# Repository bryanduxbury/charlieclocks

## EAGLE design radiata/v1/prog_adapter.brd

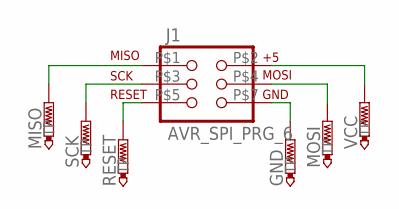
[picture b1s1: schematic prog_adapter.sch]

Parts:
GND: PTR1PAD1-17; P1-17
J1: AVR_SPI_PRG_6; 2X3_ICSP_SMD
MISO: PTR1PAD1-17; P1-17
MOSI: PTR1PAD1-17; P1-17
RESET: PTR1PAD1-17; P1-17
SCK: PTR1PAD1-17; P1-17
VCC: PTR1PAD1-17; P1-17

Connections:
unnamed: J1.P$1 (1), MISO.TP
unnamed: J1.P$3 (3), SCK.TP
unnamed: J1.P$5 (5), RESET.TP
unnamed: J1.P$2 (2), VCC.TP
unnamed: J1.P$4 (4), MOSI.TP
unnamed: GND.TP, J1.P$7 (6)

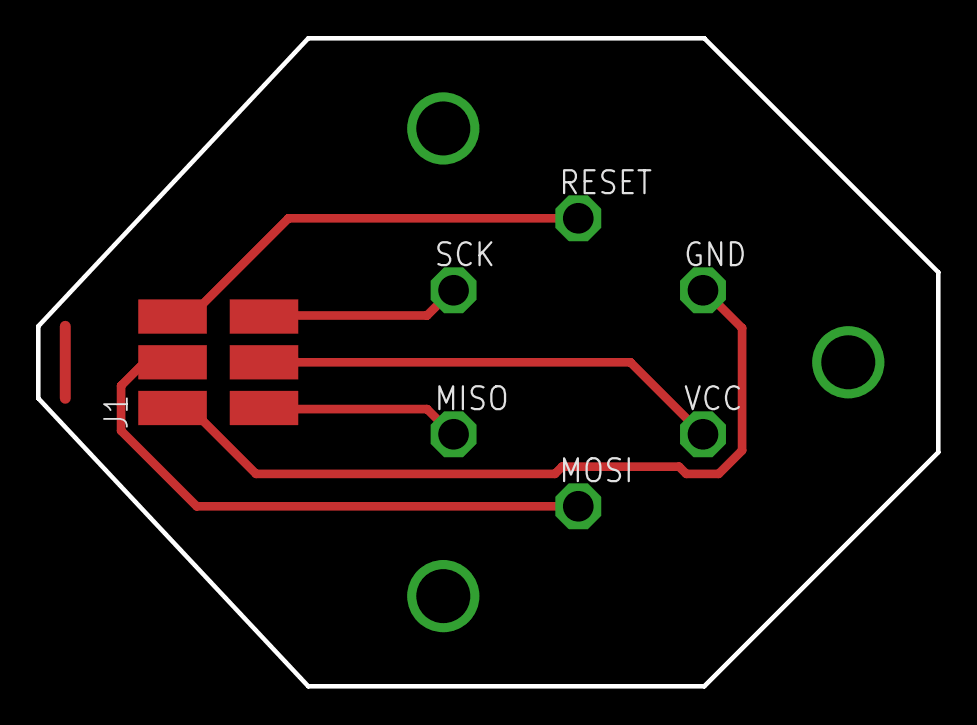
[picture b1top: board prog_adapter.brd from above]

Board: 2 copper layers, 50.0 x 36.0 mm, 7 parts (0 on the bottom side), 6 nets.

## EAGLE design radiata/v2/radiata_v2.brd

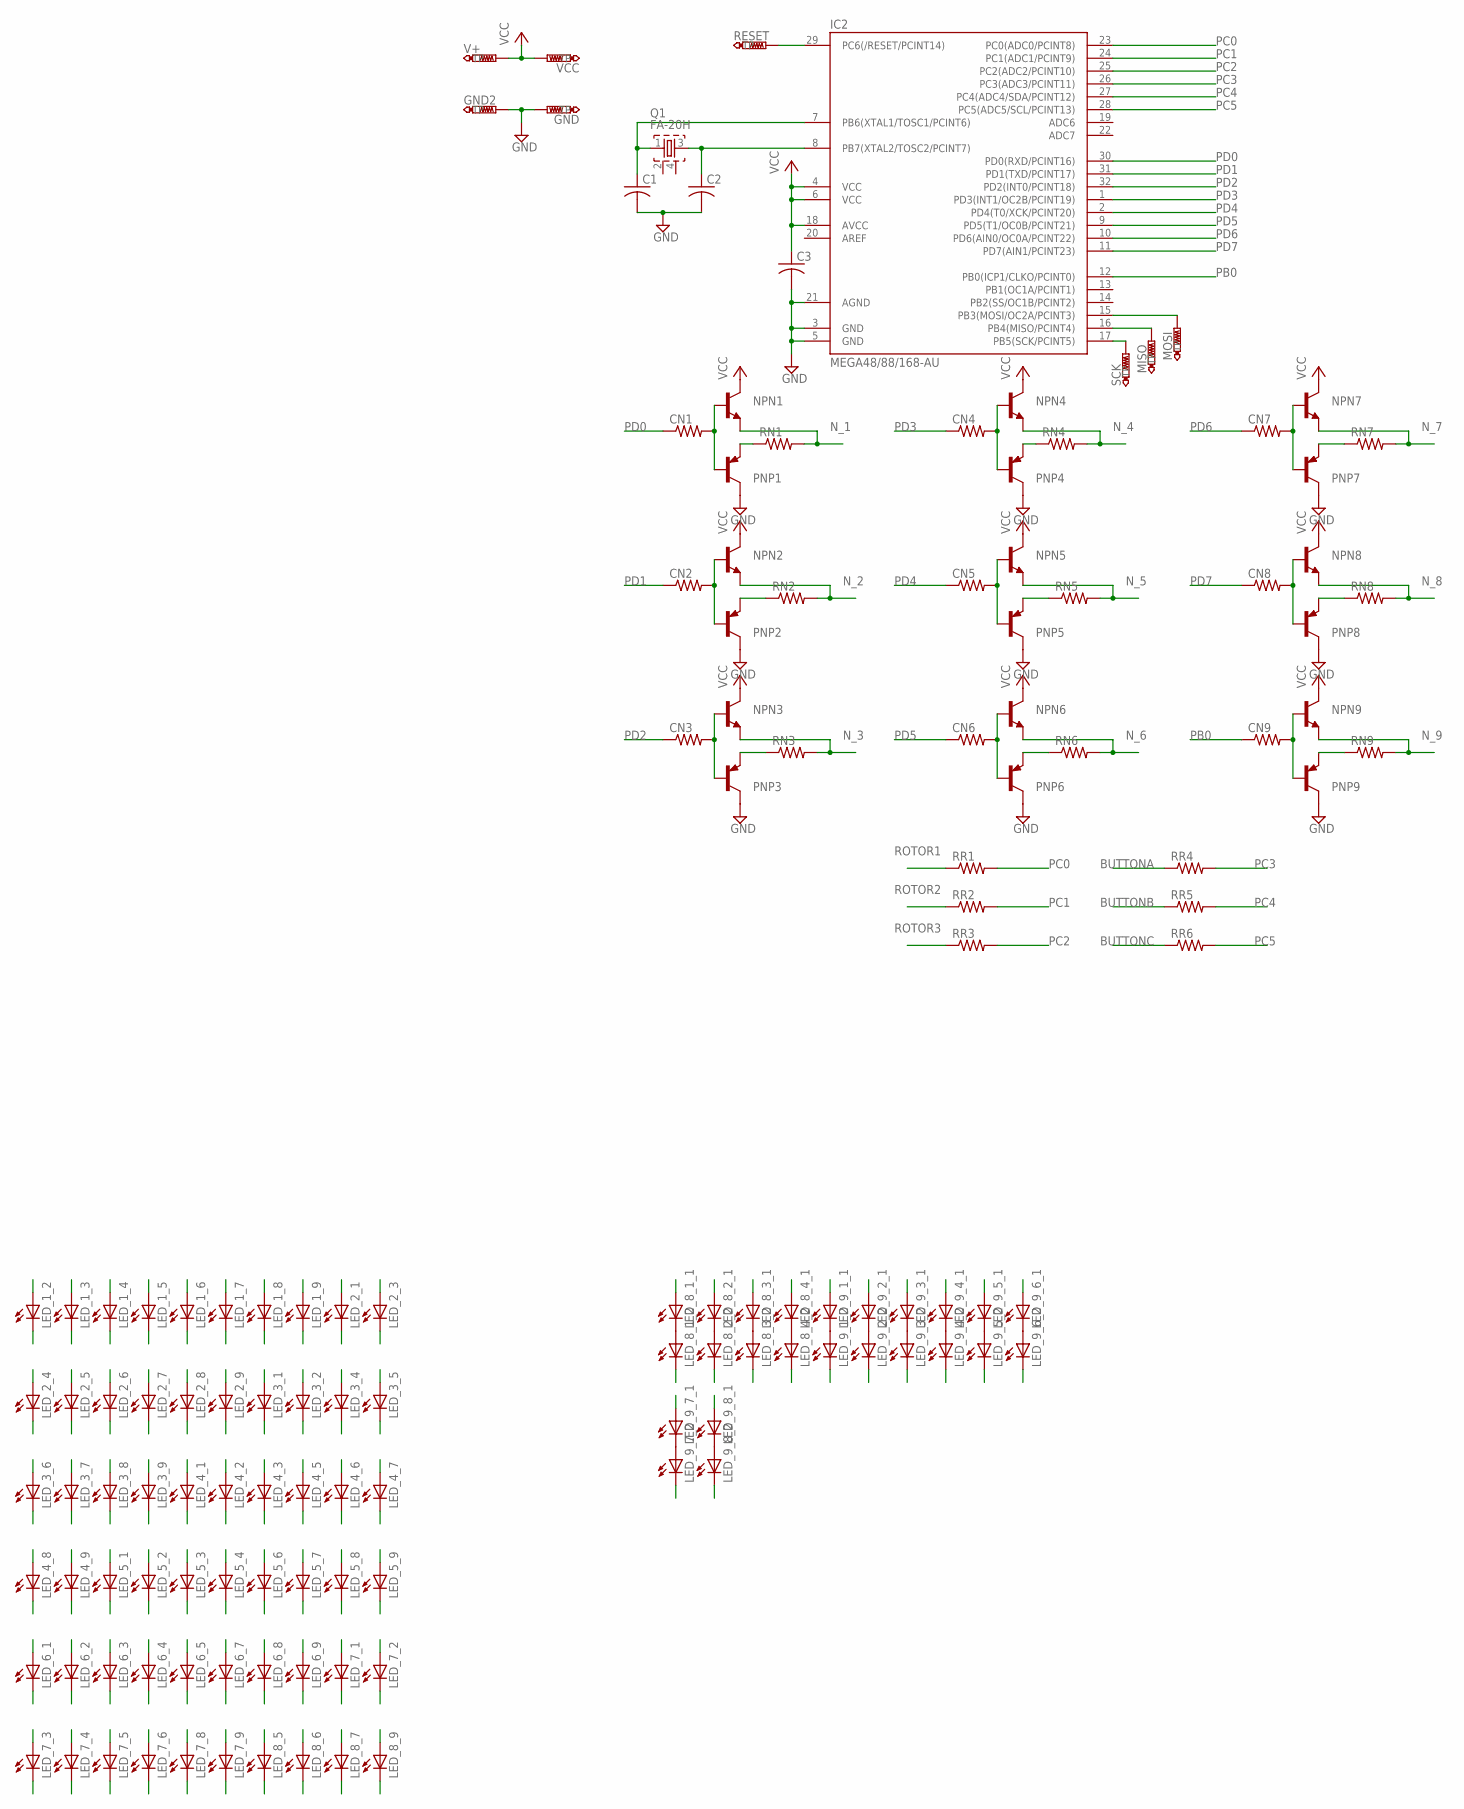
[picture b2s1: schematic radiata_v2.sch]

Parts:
C1, C2, C3: C-USC0603; C0603
CN1, CN2, CN3, CN4, CN5, CN6, CN7, CN8, CN9: R-US_M0805; M0805
GND: PTR1TP19R; TP19R
GND2: PTR1TP20SQ; TP20SQ
IC2: MEGA48/88/168-AU; TQFP32-08
LED_1_2, LED_1_3, LED_1_4, LED_1_5, LED_1_6, LED_1_7, LED_1_8, LED_1_9, LED_2_1, LED_2_3, LED_2_4, LED_2_5, LED_2_6, LED_2_7, LED_2_8, LED_2_9, LED_3_1, LED_3_2, LED_3_4, LED_3_5, LED_3_6, LED_3_7, LED_3_8, LED_3_9, LED_4_1, LED_4_2, LED_4_3, LED_4_5, LED_4_6, LED_4_7, LED_4_8, LED_4_9, LED_5_1, LED_5_2, LED_5_3, LED_5_4, LED_5_6, LED_5_7, LED_5_8, LED_5_9, LED_6_1, LED_6_2, LED_6_3, LED_6_4, LED_6_5, LED_6_7, LED_6_8, LED_6_9, LED_7_1, LED_7_2, LED_7_3, LED_7_4, LED_7_5, LED_7_6, LED_7_8, LED_7_9, LED_8_1_1, LED_8_1_2, LED_8_2_1, LED_8_2_2, LED_8_3_1, LED_8_3_2, LED_8_4_1, LED_8_4_2, LED_8_5, LED_8_6, LED_8_7, LED_8_9, LED_9_1_1, LED_9_1_2, LED_9_2_1, LED_9_2_2, LED_9_3_1, LED_9_3_2, LED_9_4_1, LED_9_4_2, LED_9_5_1, LED_9_5_2, LED_9_6_1, LED_9_6_2, LED_9_7_1, LED_9_7_2, LED_9_8_1, LED_9_8_2: LED1206; LED-1206
MISO: PTR1TP19R; TP19R
MOSI: PTR1TP19R; TP19R
NPN1, NPN2, NPN3, NPN4, NPN5, NPN6, NPN7, NPN8, NPN9: MMBT2222ALT1-NPN-SOT23-BEC; SOT23-BEC
PNP1, PNP2, PNP3, PNP4, PNP5, PNP6, PNP7, PNP8, PNP9: MMBT2907ALT1-PNP-SOT23-BEC; SOT23-BEC
Q1: FA-20H
RESET: PTR1TP19R; TP19R
RN1, RN2, RN3, RN4, RN5, RN6, RN7, RN8, RN9: RESISTOR1206; 1206
RR1, RR2, RR3, RR4, RR5, RR6: RESISTOR1206; 1206
SCK: PTR1TP19R; TP19R
V+: PTR1TP20SQ; TP20SQ
VCC: PTR1TP19R; TP19R

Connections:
BUTTONA: RR4.1
BUTTONB: RR5.1
BUTTONC: RR6.1
GND: C1.2, C2.2, C3.2, GND.TP, GND2.TP, IC2.3 (GND), IC2.5 (GND), IC2.21 (AGND), PNP1.C, PNP2.C, PNP3.C, PNP4.C, PNP5.C, PNP6.C, PNP7.C, PNP8.C, PNP9.C
unnamed: IC2.29 (PC6(/RESET/PCINT14)), RESET.TP
unnamed: IC2.17 (PB5(SCK/PCINT5)), SCK.TP
unnamed: IC2.16 (PB4(MISO/PCINT4)), MISO.TP
unnamed: IC2.15 (PB3(MOSI/OC2A/PCINT3)), MOSI.TP
unnamed: PNP1.E, RN1.1
unnamed: CN1.2, NPN1.B, PNP1.B
unnamed: PNP2.E, RN2.1
unnamed: CN2.2, NPN2.B, PNP2.B
unnamed: PNP3.E, RN3.1
unnamed: CN3.2, NPN3.B, PNP3.B
unnamed: PNP4.E, RN4.1
unnamed: CN4.2, NPN4.B, PNP4.B
unnamed: PNP5.E, RN5.1
unnamed: CN5.2, NPN5.B, PNP5.B
unnamed: PNP6.E, RN6.1
unnamed: CN6.2, NPN6.B, PNP6.B
unnamed: C2.1, IC2.8 (PB7(XTAL2/TOSC2/PCINT7)), Q1.3
unnamed: LED_8_1_1.C, LED_8_1_2.A
unnamed: LED_8_2_1.C, LED_8_2_2.A
unnamed: PNP7.E, RN7.1
unnamed: CN7.2, NPN7.B, PNP7.B
unnamed: PNP8.E, RN8.1
unnamed: CN8.2, NPN8.B, PNP8.B
unnamed: PNP9.E, RN9.1
unnamed: CN9.2, NPN9.B, PNP9.B
unnamed: LED_8_3_1.C, LED_8_3_2.A
unnamed: LED_8_4_1.C, LED_8_4_2.A
unnamed: LED_9_1_1.C, LED_9_1_2.A
unnamed: LED_9_2_1.C, LED_9_2_2.A
unnamed: LED_9_3_1.C, LED_9_3_2.A
unnamed: LED_9_4_1.C, LED_9_4_2.A
unnamed: LED_9_5_1.C, LED_9_5_2.A
unnamed: LED_9_6_1.C, LED_9_6_2.A
unnamed: LED_9_7_1.C, LED_9_7_2.A
unnamed: LED_9_8_1.C, LED_9_8_2.A
N_1: LED_1_2.A, LED_1_3.A, LED_1_4.A, LED_1_5.A, LED_1_6.A, LED_1_7.A, LED_1_8.A, LED_1_9.A, LED_2_1.C, LED_3_1.C, LED_4_1.C, LED_5_1.C, LED_6_1.C, LED_7_1.C, LED_8_1_2.C, LED_9_1_2.C, NPN1.E, RN1.2
N_2: LED_1_2.C, LED_2_1.A, LED_2_3.A, LED_2_4.A, LED_2_5.A, LED_2_6.A, LED_2_7.A, LED_2_8.A, LED_2_9.A, LED_3_2.C, LED_4_2.C, LED_5_2.C, LED_6_2.C, LED_7_2.C, LED_8_2_2.C, LED_9_2_2.C, NPN2.E, RN2.2
N_3: LED_1_3.C, LED_2_3.C, LED_3_1.A, LED_3_2.A, LED_3_4.A, LED_3_5.A, LED_3_6.A, LED_3_7.A, LED_3_8.A, LED_3_9.A, LED_4_3.C, LED_5_3.C, LED_6_3.C, LED_7_3.C, LED_8_3_2.C, LED_9_3_2.C, NPN3.E, RN3.2
N_4: LED_1_4.C, LED_2_4.C, LED_3_4.C, LED_4_1.A, LED_4_2.A, LED_4_3.A, LED_4_5.A, LED_4_6.A, LED_4_7.A, LED_4_8.A, LED_4_9.A, LED_5_4.C, LED_6_4.C, LED_7_4.C, LED_8_4_2.C, LED_9_4_2.C, NPN4.E, RN4.2
N_5: LED_1_5.C, LED_2_5.C, LED_3_5.C, LED_4_5.C, LED_5_1.A, LED_5_2.A, LED_5_3.A, LED_5_4.A, LED_5_6.A, LED_5_7.A, LED_5_8.A, LED_5_9.A, LED_6_5.C, LED_7_5.C, LED_8_5.C, LED_9_5_2.C, NPN5.E, RN5.2
N_6: LED_1_6.C, LED_2_6.C, LED_3_6.C, LED_4_6.C, LED_5_6.C, LED_6_1.A, LED_6_2.A, LED_6_3.A, LED_6_4.A, LED_6_5.A, LED_6_7.A, LED_6_8.A, LED_6_9.A, LED_7_6.C, LED_8_6.C, LED_9_6_2.C, NPN6.E, RN6.2
N_7: LED_1_7.C, LED_2_7.C, LED_3_7.C, LED_4_7.C, LED_5_7.C, LED_6_7.C, LED_7_1.A, LED_7_2.A, LED_7_3.A, LED_7_4.A, LED_7_5.A, LED_7_6.A, LED_7_8.A, LED_7_9.A, LED_8_7.C, LED_9_7_2.C, NPN7.E, RN7.2
N_8: LED_1_8.C, LED_2_8.C, LED_3_8.C, LED_4_8.C, LED_5_8.C, LED_6_8.C, LED_7_8.C, LED_8_1_1.A, LED_8_2_1.A, LED_8_3_1.A, LED_8_4_1.A, LED_8_5.A, LED_8_6.A, LED_8_7.A, LED_8_9.A, LED_9_8_2.C, NPN8.E, RN8.2
N_9: LED_1_9.C, LED_2_9.C, LED_3_9.C, LED_4_9.C, LED_5_9.C, LED_6_9.C, LED_7_9.C, LED_8_9.C, LED_9_1_1.A, LED_9_2_1.A, LED_9_3_1.A, LED_9_4_1.A, LED_9_5_1.A, LED_9_6_1.A, LED_9_7_1.A, LED_9_8_1.A, NPN9.E, RN9.2
PB0: CN9.1, IC2.12 (PB0(ICP1/CLKO/PCINT0))
PB1: C1.1, IC2.7 (PB6(XTAL1/TOSC1/PCINT6)), Q1.1
PC0: IC2.23 (PC0(ADC0/PCINT8)), RR1.2
PC1: IC2.24 (PC1(ADC1/PCINT9)), RR2.2
PC2: IC2.25 (PC2(ADC2/PCINT10)), RR3.2
PC3: IC2.26 (PC3(ADC3/PCINT11)), RR4.2
PC4: IC2.27 (PC4(ADC4/SDA/PCINT12)), RR5.2
PC5: IC2.28 (PC5(ADC5/SCL/PCINT13)), RR6.2
PD0: CN1.1, IC2.30 (PD0(RXD/PCINT16))
PD1: CN2.1, IC2.31 (PD1(TXD/PCINT17))
PD2: CN3.1, IC2.32 (PD2(INT0/PCINT18))
PD3: CN4.1, IC2.1 (PD3(INT1/OC2B/PCINT19))
PD4: CN5.1, IC2.2 (PD4(T0/XCK/PCINT20))
PD5: CN6.1, IC2.9 (PD5(T1/OC0B/PCINT21))
PD6: CN7.1, IC2.10 (PD6(AIN0/OC0A/PCINT22))
PD7: CN8.1, IC2.11 (PD7(AIN1/PCINT23))
ROTOR1: RR1.1
ROTOR2: RR2.1
ROTOR3: RR3.1
VCC: C3.1, IC2.4 (VCC), IC2.6 (VCC), IC2.18 (AVCC), NPN1.C, NPN2.C, NPN3.C, NPN4.C, NPN5.C, NPN6.C, NPN7.C, NPN8.C, NPN9.C, V+.TP, VCC.TP

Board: 2 copper layers, 139 parts (15 on the bottom side), 62 nets, no tracks yet.

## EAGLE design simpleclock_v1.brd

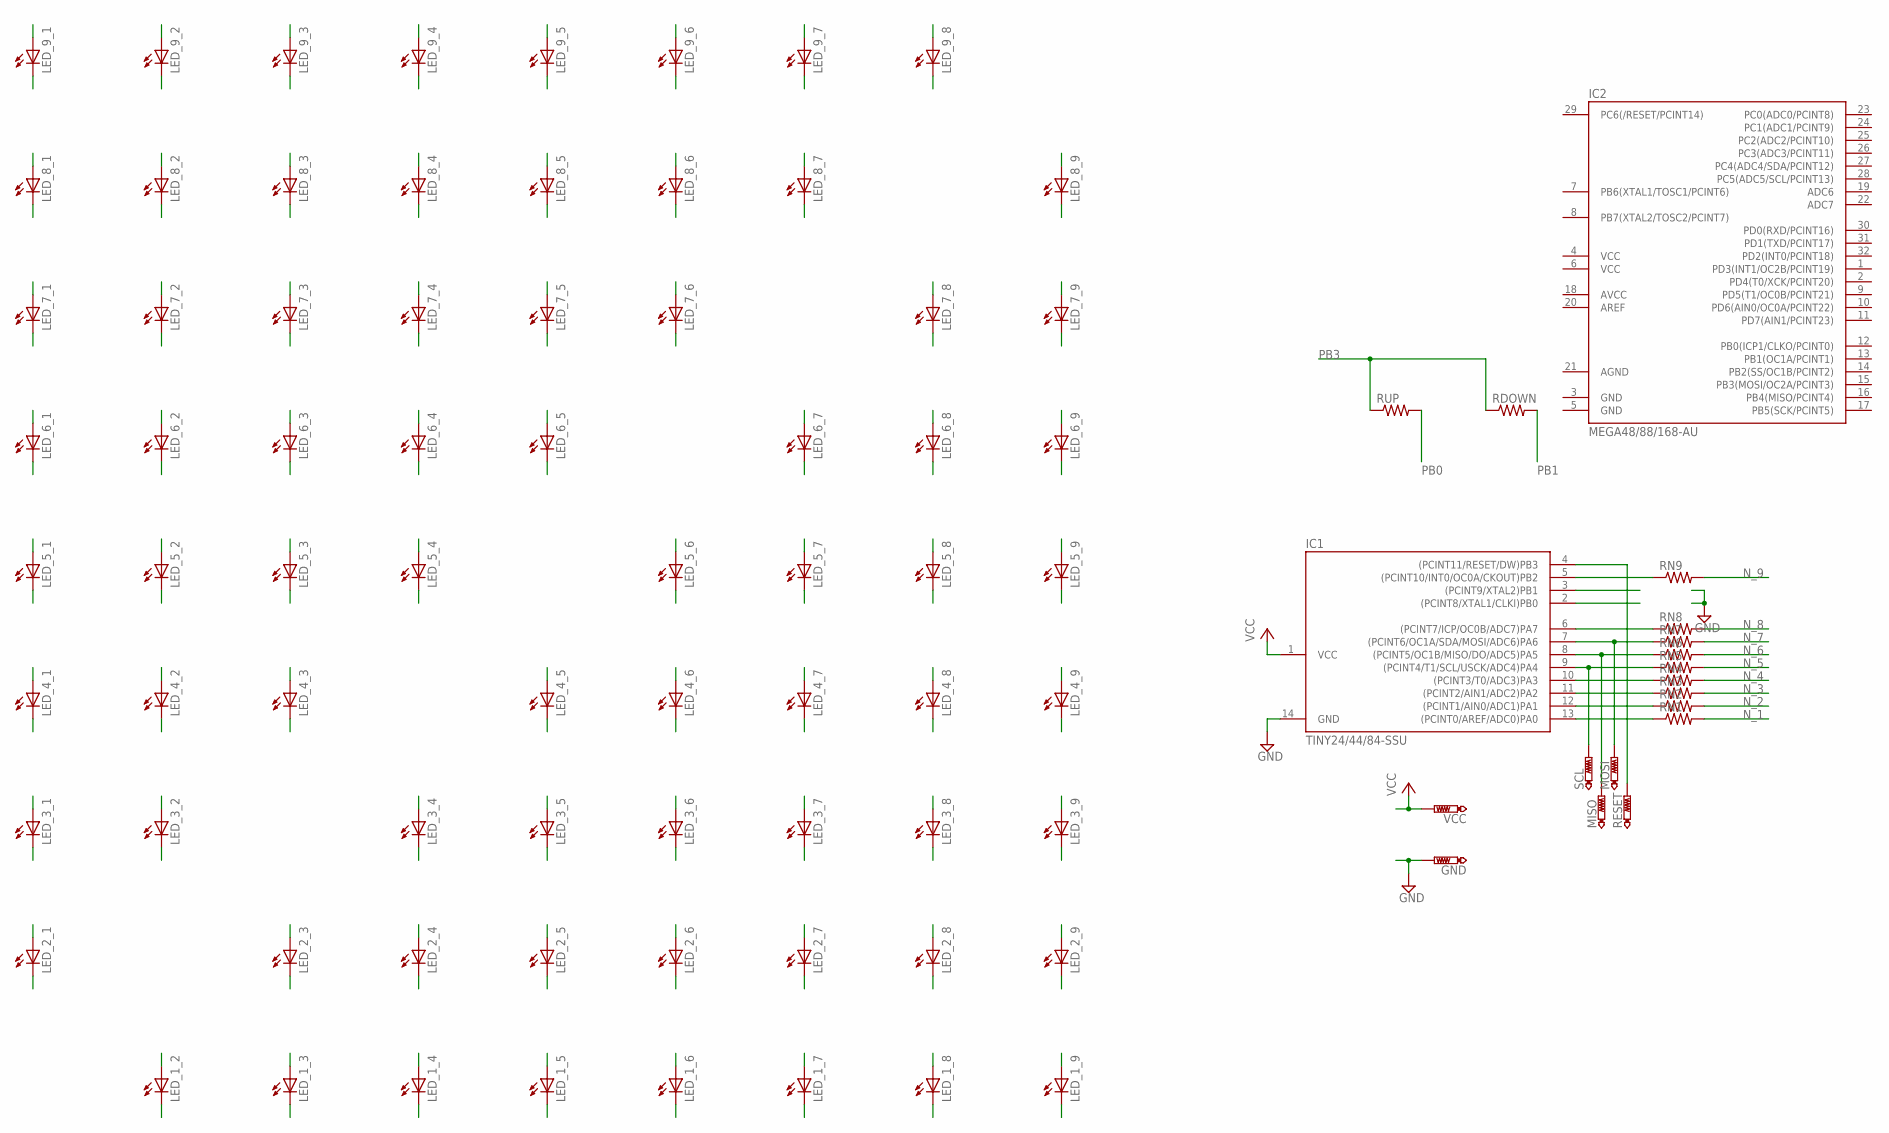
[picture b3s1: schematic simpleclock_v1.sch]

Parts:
GND: PTR1PAD1-13; P1-13
IC1: TINY24/44/84-SSU; SOIC14
IC2: MEGA48/88/168-AU; TQFP32-08
LED_1_2, LED_1_3, LED_1_4, LED_1_5, LED_1_6, LED_1_7, LED_1_8, LED_1_9, LED_2_1, LED_2_3, LED_2_4, LED_2_5, LED_2_6, LED_2_7, LED_2_8, LED_2_9, LED_3_1, LED_3_2, LED_3_4, LED_3_5, LED_3_6, LED_3_7, LED_3_8, LED_3_9, LED_4_1, LED_4_2, LED_4_3, LED_4_5, LED_4_6, LED_4_7, LED_4_8, LED_4_9, LED_5_1, LED_5_2, LED_5_3, LED_5_4, LED_5_6, LED_5_7, LED_5_8, LED_5_9, LED_6_1, LED_6_2, LED_6_3, LED_6_4, LED_6_5, LED_6_7, LED_6_8, LED_6_9, LED_7_1, LED_7_2, LED_7_3, LED_7_4, LED_7_5, LED_7_6, LED_7_8, LED_7_9, LED_8_1, LED_8_2, LED_8_3, LED_8_4, LED_8_5, LED_8_6, LED_8_7, LED_8_9, LED_9_1, LED_9_2, LED_9_3, LED_9_4, LED_9_5, LED_9_6, LED_9_7, LED_9_8: LEDCHIPLED_1206; CHIPLED_1206
MISO: PTR1PAD1-13; P1-13
MOSI: PTR1PAD1-13; P1-13
RDOWN: RESISTOR1206; 1206
RESET: PTR1PAD1-13; P1-13
RN1, RN2, RN3, RN4, RN5, RN6, RN7, RN8, RN9: RESISTOR1206; 1206
RUP: RESISTOR1206; 1206
SCL: PTR1PAD1-13; P1-13
VCC: PTR1PAD1-13; P1-13

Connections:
AGND: IC2.21 (AGND)
GND: GND.TP, IC1.14 (GND), IC2.3 (GND), IC2.5 (GND)
N_1: LED_1_2.A, LED_1_3.A, LED_1_4.A, LED_1_5.A, LED_1_6.A, LED_1_7.A, LED_1_8.A, LED_1_9.A, LED_2_1.C, LED_3_1.C, LED_4_1.C, LED_5_1.C, LED_6_1.C, LED_7_1.C, LED_8_1.C, LED_9_1.C, RN1.2
N_2: LED_1_2.C, LED_2_1.A, LED_2_3.A, LED_2_4.A, LED_2_5.A, LED_2_6.A, LED_2_7.A, LED_2_8.A, LED_2_9.A, LED_3_2.C, LED_4_2.C, LED_5_2.C, LED_6_2.C, LED_7_2.C, LED_8_2.C, LED_9_2.C, RN2.2
N_3: LED_1_3.C, LED_2_3.C, LED_3_1.A, LED_3_2.A, LED_3_4.A, LED_3_5.A, LED_3_6.A, LED_3_7.A, LED_3_8.A, LED_3_9.A, LED_4_3.C, LED_5_3.C, LED_6_3.C, LED_7_3.C, LED_8_3.C, LED_9_3.C, RN3.2
N_4: LED_1_4.C, LED_2_4.C, LED_3_4.C, LED_4_1.A, LED_4_2.A, LED_4_3.A, LED_4_5.A, LED_4_6.A, LED_4_7.A, LED_4_8.A, LED_4_9.A, LED_5_4.C, LED_6_4.C, LED_7_4.C, LED_8_4.C, LED_9_4.C, RN4.2
N_5: LED_1_5.C, LED_2_5.C, LED_3_5.C, LED_4_5.C, LED_5_1.A, LED_5_2.A, LED_5_3.A, LED_5_4.A, LED_5_6.A, LED_5_7.A, LED_5_8.A, LED_5_9.A, LED_6_5.C, LED_7_5.C, LED_8_5.C, LED_9_5.C, RN5.2
N_6: LED_1_6.C, LED_2_6.C, LED_3_6.C, LED_4_6.C, LED_5_6.C, LED_6_1.A, LED_6_2.A, LED_6_3.A, LED_6_4.A, LED_6_5.A, LED_6_7.A, LED_6_8.A, LED_6_9.A, LED_7_6.C, LED_8_6.C, LED_9_6.C, RN6.2
N_7: LED_1_7.C, LED_2_7.C, LED_3_7.C, LED_4_7.C, LED_5_7.C, LED_6_7.C, LED_7_1.A, LED_7_2.A, LED_7_3.A, LED_7_4.A, LED_7_5.A, LED_7_6.A, LED_7_8.A, LED_7_9.A, LED_8_7.C, LED_9_7.C, RN7.2
N_8: LED_1_8.C, LED_2_8.C, LED_3_8.C, LED_4_8.C, LED_5_8.C, LED_6_8.C, LED_7_8.C, LED_8_1.A, LED_8_2.A, LED_8_3.A, LED_8_4.A, LED_8_5.A, LED_8_6.A, LED_8_7.A, LED_8_9.A, LED_9_8.C, RN8.2
N_9: LED_1_9.C, LED_2_9.C, LED_3_9.C, LED_4_9.C, LED_5_9.C, LED_6_9.C, LED_7_9.C, LED_8_9.C, LED_9_1.A, LED_9_2.A, LED_9_3.A, LED_9_4.A, LED_9_5.A, LED_9_6.A, LED_9_7.A, LED_9_8.A, RN9.2
PA0: IC1.13 ((PCINT0/AREF/ADC0)PA0), RN1.1
PA1: IC1.12 ((PCINT1/AIN0/ADC1)PA1), RN2.1
PA2: IC1.11 ((PCINT2/AIN1/ADC2)PA2), RN3.1
PA3: IC1.10 ((PCINT3/T0/ADC3)PA3), RN4.1
PA4: IC1.9 ((PCINT4/T1/SCL/USCK/ADC4)PA4), RN5.1, SCL.TP
PA5: IC1.8 ((PCINT5/OC1B/MISO/DO/ADC5)PA5), MISO.TP, RN6.1
PA6: IC1.7 ((PCINT6/OC1A/SDA/MOSI/ADC6)PA6), MOSI.TP, RN7.1
PA7: IC1.6 ((PCINT7/ICP/OC0B/ADC7)PA7), RN8.1
PB0: IC1.2 ((PCINT8/XTAL1/CLKI)PB0), RUP.2
PB1: IC1.3 ((PCINT9/XTAL2)PB1), RDOWN.2
PB2: IC1.5 ((PCINT10/INT0/OC0A/CKOUT)PB2), RN9.1
PB3: IC1.4 ((PCINT11/RESET/DW)PB3), RDOWN.1, RESET.TP, RUP.1
VCC: IC1.1 (VCC), IC2.4 (VCC), IC2.6 (VCC), VCC.TP

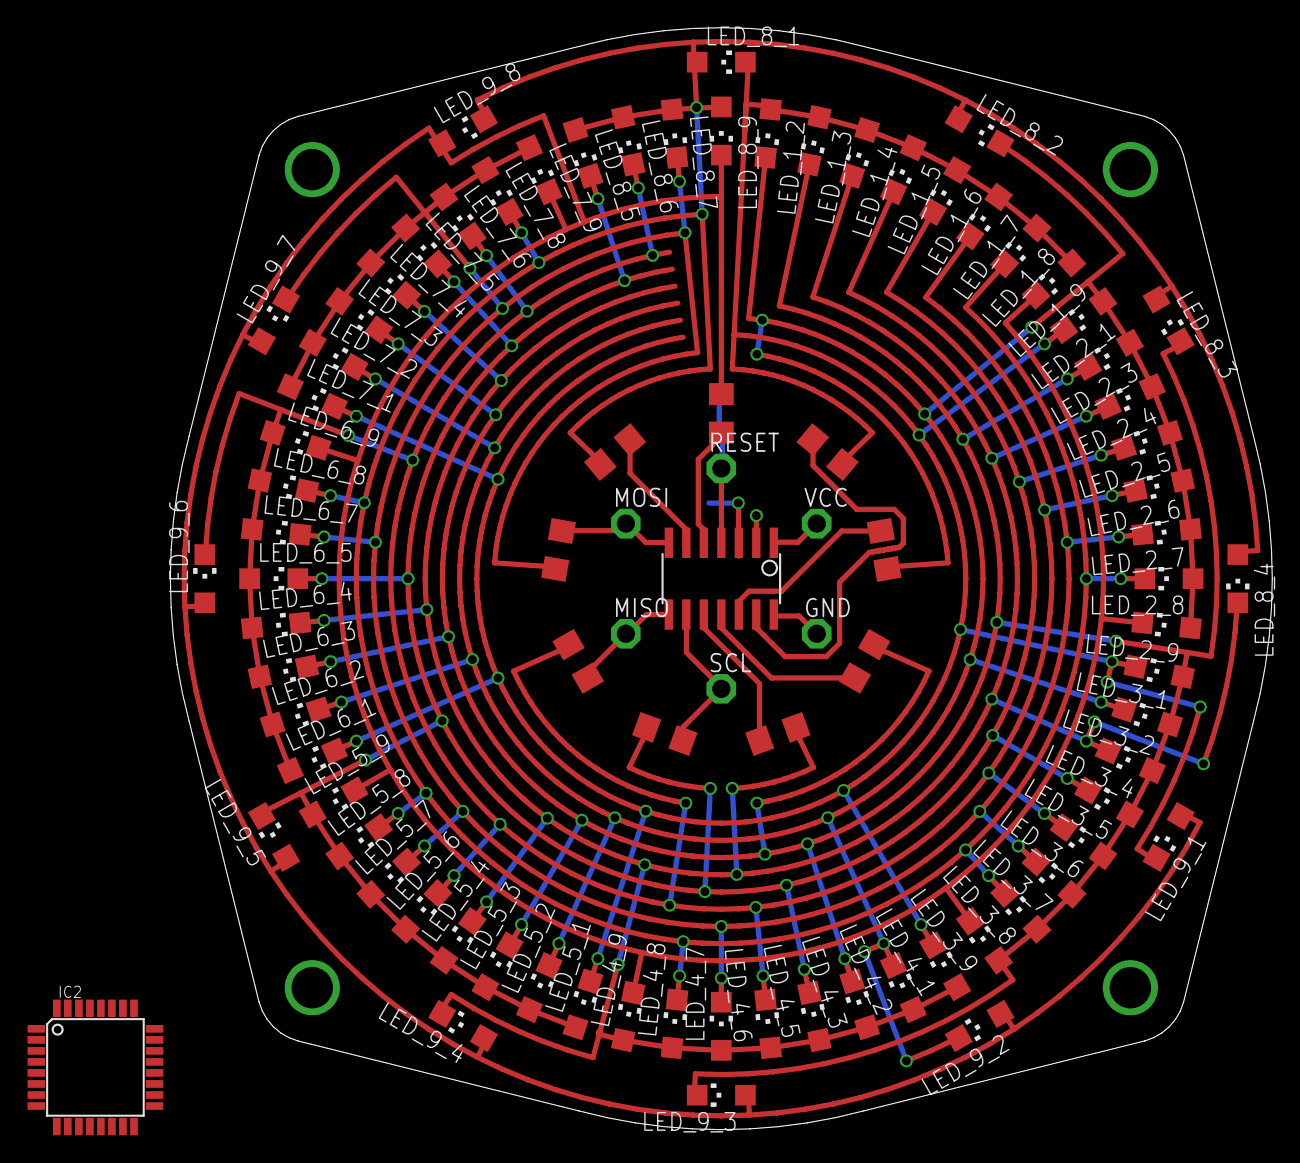
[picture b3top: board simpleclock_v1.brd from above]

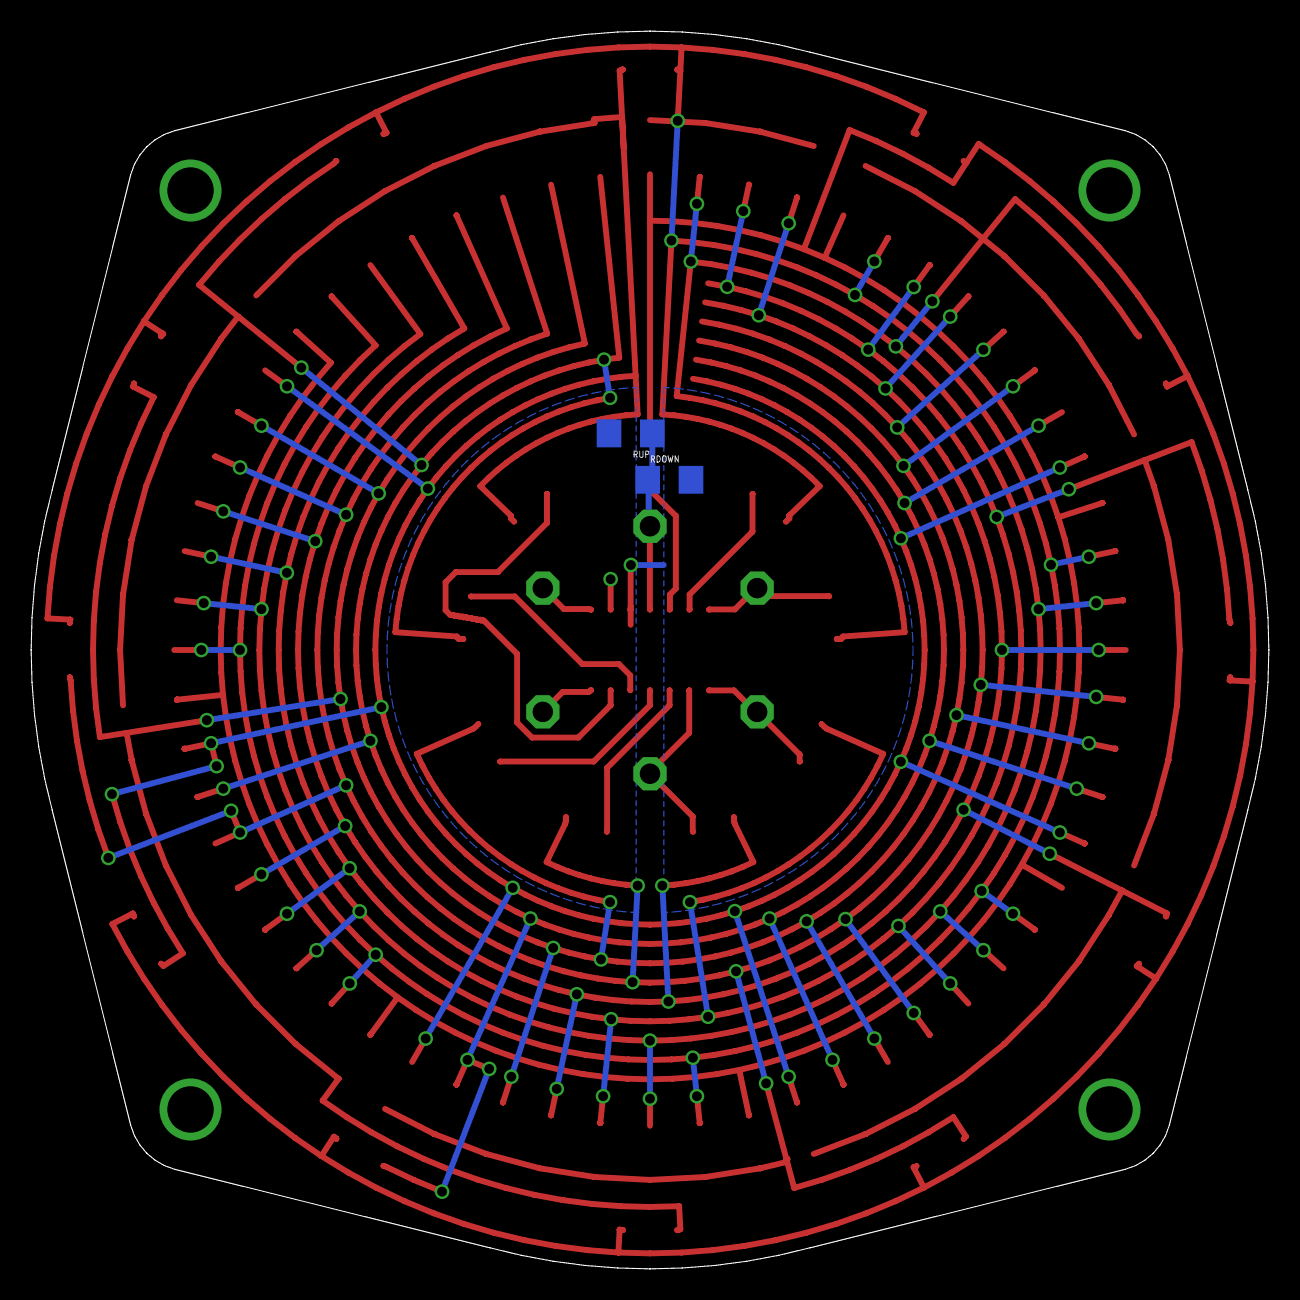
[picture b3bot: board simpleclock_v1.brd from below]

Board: 2 copper layers, 80.0 x 80.0 mm, 91 parts (2 on the bottom side), 23 nets.

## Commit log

2013-09-09 init commit (finally)
2013-09-09 gitignore
2013-09-10 lots more traces routed
2013-09-22 wow, it's been that long since i committed?
2013-11-09 new board outline
2013-11-13 rename simpleclock to 'radiata'
2013-11-15 reroute the outer leds so that the scroll rotor can fit into the space under the inner leds
2013-11-15 fix a routing issue; adjust scroll rotor size
2013-11-17 lots of progress, driving towards a scroll wheel that passes DRC
2013-11-27 add push/pull resistors
2013-12-06 some cleanup in the scroll wheel scad
2013-12-06 ignore generated eagle script files
2013-12-06 added a few more components and the signature blob to the components
2013-12-06 final versions of board and schematic
2013-12-06 move all the radiata stuff down a level into their own folder
2013-12-07 added design for programming adapter
2013-12-18 mocked pcba scad model to design around
2013-12-18 misc changes to programming adapter board
2013-12-18 added programming points to the pcba mockup; first rev of assembled enclosure
2013-12-29 first commit for radiata firmware
2013-12-29 wip for enclosure + stand
2013-12-29 fix the programming adapter board to actually mate with the real pcb
2013-12-31 lots of random exploration
2013-12-31 fix the prog adapter board to actually match the correct pinout
2013-12-31 looks like using the 3-sigma approach has improved the sensitivity
2014-01-05 added the suppress method to MonoCap; didn't make a huge difference :(
2014-01-15 almost done with the enclosure
2014-01-16 add tabs to stand sides and back retainer
2014-01-16 kerf adjust the stand side piece
2014-01-18 add top level time-based-rotate for animated giffing
2014-02-02 move all the v1 files into v1 dir
2014-02-02 everything
2014-02-02 thicken the midring and adjust screw hole sizes
2014-02-03 clean out exported dxfs
2014-02-03 replace a bunch of constants with variables
2014-02-27 strip firmware down to bare minimum
2014-02-27 fix the firmware to actually keep decent time; tested-working version of the programming remote

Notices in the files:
parts and their libraries:
SparkFun: Licensing: CC v3.0 Share-Alike You are welcome to use this library for commercial purposes.
